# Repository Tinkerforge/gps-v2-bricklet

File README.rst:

GPS Bricklet 2.0
================

This repository contains the firmware source code and the hardware design
files. The documentation generator configs can be found at
https://github.com/Tinkerforge/generators

Repository Content
------------------

software/:
 * examples/: Examples for all supported languages
 * build/: Compiled files
 * src/: Source code of firmware
 * Makefile: Makefile to build project

hardware/:
 * Contains KiCad project files and additionally schematics as PDF

datasheets/:
 * Contains datasheets for sensors and complex ICs that are used

Hardware
--------

The hardware is designed with the open source EDA Suite KiCad
(http://www.kicad.org). Before you are able to open the files,
you have to install the Tinkerforge kicad-libraries
(https://github.com/Tinkerforge/kicad-libraries). You can either clone
them directly in hardware/ or clone them in a separate folder and
symlink them into hardware/
(ln -s kicad_path/kicad-libraries project_path/hardware). After that you
can open the .pro file in hardware/ with KiCad and from there view and
modify the schematics and the PCB layout.

Software
--------

If you want to do your own Brick/Bricklet firmware development we highly
recommend that you use our build environment setup script and read the
tutorial (https://www.tinkerforge.com/en/doc/Tutorials/Tutorial_Build_Environment/Tutorial.html).

To compile the C code we recommend you to install the newest GNU Arm Embedded
Toolchain (https://launchpad.net/gcc-arm-embedded/+download).
You also need to install bricklib2 (https://github.com/Tinkerforge/bricklib2).

You can either clone it directly in software/src/ or clone it in a
separate folder and symlink it into software/src/
(ln -s bricklib_path/bricklib2 project_path/software/src/). Finally make sure to
have CMake installed (http://www.cmake.org/cmake/resources/software.html).

After that you can build the firmware by invoking make in software/.
The firmware (.zbin) can then be found in software/build/ and uploaded
with brickv (click button "Flashing" on start screen).

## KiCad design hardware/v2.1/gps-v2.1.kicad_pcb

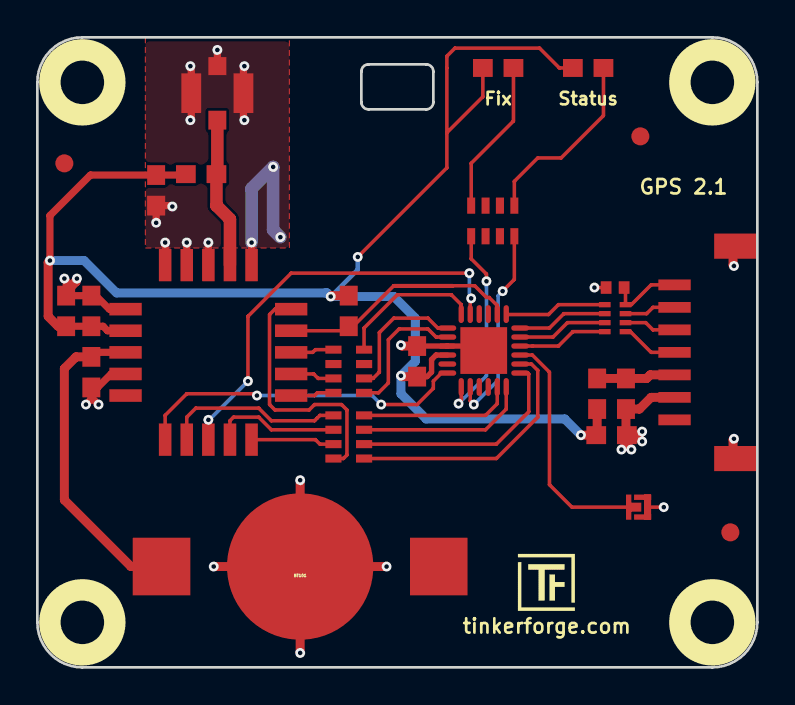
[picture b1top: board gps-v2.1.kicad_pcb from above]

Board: 2 copper layers, 40.0 x 35.0 mm, 32 parts (2 on the bottom side), 35 nets.

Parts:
BT101: Battery; BATTERY_HOLDER_BK870
C1: 220pF; C0402F
C101, C105: 1uF; C0603E
C102: 10uF; C0603E
C103, C104: 100nF; C0603E
C106, C107: 1µF; C0603E
D101: LED blue; D0603E
D102: LED green; D0603E
FB101: FB; C0603E
Fiducial_Mark: VAL**; Fiducial_Mark
Fiducial_Mark#2, Fiducial_Mark#3: VAL**; Fiducial_Mark
L101: 33nH; R0603E
P101: CON-SENSOR; CON-SENSOR2
P103: Boot; SolderJumper
P104: U.FL; U.FL-CON
R102: 1k; R0603E
RP2: 82; 4X0402
RP101, RP102: 270; 0603X4
RP103: 1k; 0603X4
U101: XMC1302-32; QFN24-4x4mm-0.5mm
U102: FireFlyX1
U103, U104, U105, U106: DRILL; DRILL_NP
VAL: WEEE_7mm_back
VAL#2: CE_5mm

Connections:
1PPS: RP101.4, U101.6
GND: BT101.2, C1.2, C101.1, C102.1, C103.1, C104.1, C105.1, C106.1, C107.1, P101.2, P101.EP, P103.1, P104.2, U101.9, U101.EXP, U102.1, U102.3, U102.4, U102.5, U102.6, U102.9
INT: U101.5, U102.13
M-CLK: RP102.6, U101.19
M-CS: RP102.5, U101.20
M-MISO: RP102.8, U101.17
M-MOSI: RP102.7, U101.18
unnamed: C1.1, P101.7, RP2.4
unnamed: C101.2, FB101.2, P101.3
unnamed: D101.2, RP103.1
unnamed: D102.2, RP103.4
unnamed: L101.2, P104.1, U102.2
unnamed: P101.4, RP2.1
unnamed: P101.5, RP2.2
unnamed: P101.6, RP2.3
unnamed: P103.2, U101.21
unnamed: RP101.5, U102.18
unnamed: RP101.7, U102.17
unnamed: RP101.8, U102.16
unnamed: RP102.1, U102.12
unnamed: RP102.2, U102.14
unnamed: RP102.3, U102.15
unnamed: RP102.4, U102.20
unnamed: RP103.5, U101.13
unnamed: RP103.8, U101.14
RESET: R102.2, U101.2, U102.19
RTCM: U101.12, U102.11
RXD: RP101.2, U101.7
S-CLK: RP2.7, U101.23
S-CS: RP2.8, U101.22
S-MISO: RP2.5, U101.1
S-MOSI: RP2.6, U101.24
TXD: RP101.1, U101.8
VBat: BT101.1, C106.2, U102.8
VCC: C102.2, C103.2, C104.2, C105.2, C107.2, D101.1, D102.1, FB101.1, L101.1, R102.1, U101.10, U102.7

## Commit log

2016-09-02 Add readme
2016-09-02 Add initial firmware with bootloader support
2016-09-06 Add system timer
2016-09-06 Better formating for custom command
2016-09-06 Add PRE_BUILD touch and make clean for brickletboot
2016-09-07 Add wait state comment
2016-09-14 datasheets
2016-09-15 Add new source files to Makefile
2016-09-15 Add stub for communication
2016-09-15 Use four DMA channels (2x bootloader SPI and 2x firmware SPI)
2016-09-15 Enable third clock with more precise 8MHz input
2016-09-15 Update logging configuration
2016-09-15 Use new bootloader_ functions to call bootloader init and tick
2016-09-15 Add FireFly X1 driver stub
2016-09-15 Add FireFly X1 driver config
2016-09-15 Add minmea lib (small NMEA parser)
2016-09-22 Add asf_overwrite config
2016-09-22 Change default optimization to Os
2016-09-22 Add asf overwrites
2016-09-22 Use nostartfiles and nono.specs flags for firmware
2016-09-22 Add libgcc static compliles that use division implementation of bootloader
2016-09-22 Update configs
2016-09-22 Add state machine, use bootloader functions
2016-09-22 Remove bootloader_init and debug output (bootloader_init now called during startup)
2016-10-12 Add temporary debug
2016-10-19 adding hardware prototype for new version with co-processor
2016-10-19 change battery holder to version for cr-1025
2016-11-03 Port GPS V2 stub implementation from samd to XMC
2016-11-08 Add automatic build support for bootstrapper
2016-11-09 Fix error in bootstrapper copy logic
2016-11-10 Add firefly and minmea file
2016-11-10 Change default debug pin to boot pin
2016-11-10 Add enhanced bootloader configuration
2016-11-10 Port Firefly X1 configuration from samd to xmc1
2016-11-10 SPI config not needed anymore
2016-11-10 Port Firefly X1 readout implementation from samd to xmc1 (WIP)
2016-11-10 Add firefly init and tick to main again
2016-11-11 remove boot description
2016-11-11 Add stub implementation for API
2016-11-11 Add ringbuffer for incoming data, parse incoming data into structs that hold all of current data
2016-11-11 Use auto-generated communication.c/h
2016-11-14 Change co MCU type to XMC1100_Q024x0016
2016-11-14 Add support for custom cmake config in brickletboot and bootstrapper
2016-11-14 Add custom cmake config
2016-11-14 Use cmake config defines from bricklib2
2016-11-14 Add correct flash origin and size to cmake configs
2016-11-14 Change linker script name
2016-11-17 System timer initialization now done during startup, before main is called
2016-11-17 Use proper indentation
2016-11-17 Remove unused defines
2016-11-17 Fix typo
2016-11-17 Add data pointer, size and limit defines
2016-12-08 Add communication_callback.c to Makefile
2016-12-08 Use 32kb flash size
2016-12-08 Fill in communication data
2016-12-08 Add missing custom bootloader configuration
2016-12-08 Add reset function handling
2016-12-08 Add support for glonass sats
2016-12-08 Add support for detection of new values
2016-12-08 Firmware version should start with 2.0.0
2016-12-08 Remove debugging
2016-12-08 Add constants, restart and new_* variables
2016-12-08 Add communication callback init and tick
2016-12-08 Remove debug
2016-12-08 Simplify callback handling
2016-12-15 fix pin mapping
2016-12-15 Add fix LED configuration and logic
2016-12-15 Add comments for new release version pinouts
2017-01-03 remove silkscreen areas around leds
2017-01-04 drc check, change reset pullup 10k->1k
2017-01-04 add fiducials
2017-01-10 change bricklet connector to 7pole JST GH
2017-01-10 fix grid origin
2017-01-12 change via size, add spi pulldowns for inputs
2017-01-18 ange serial resistor values
2017-01-19 Change MCU to 1302
2017-01-19 Use release version pins
2017-01-19 Add EEPROM emulation size
2017-01-19 Add eeprom page read/write bootloader function define
2017-01-20 Add FireFly X1 datasheet
2017-01-23 Add bootstrapper config
2017-01-31 slot for external antenna added
2017-02-07 add license file
2017-02-07 remove old datasheet
2017-03-07 Fix scale factors for altitude and height to give cm
2017-03-10 Make sure fix LED blinks if fix quality is 0
2017-03-10 Change fix LED to just be on or off to indicate fix
    Also add PPS mode for fix LED.
2017-04-12 Add rx/tx information to allow for hald-fuplex bootstrapper flashing
2017-05-10 Fine-tune naming
2017-05-11 Prepare satellite numbers array for streaming
2017-05-11 Add examples
2017-05-11 Update changelog
2017-05-11 Remove WIP marker
2017-05-31 Report speed correctly as km/h instead of knots
2017-06-02 octave: Use javaObject instead of deprecated java_new
2017-06-16 Add 3d information (tbc)
2017-06-23 Add 3d information (final)
2017-06-23 Add 3d model (*.FCStd and *.STEP)
2017-07-12 add missing schematic
2017-08-31 Reset FireflyX1 if it doesn't talk to us anymore
    If we don't get an interrupt for a long time we first try to
    read from it without interrupt. If we don't get any data back we
    reset the IC.
2017-08-31 Add missing 2.0.1 ref to changelog
2017-09-01 Increase SPI speed to 200kHz
    200kHz is definitely fast enough to receive all data with 10Hz update rate
2017-09-01 Fix ms/us mixup
2017-09-01 Add SBAS enable/disable support and API
2017-09-06 Decrease baudrate to 100000 again
    This seems to be enough for the full 10Hz of data
2017-09-06 Increase version to 2.0.2
2017-09-06 Add changelog for 2.0.2
2017-09-19 specify processor
2017-11-06 update u.fl footprint
2017-11-13 Fix schematic PDF: processor type was unspecified
2017-11-30 Update examples from generator
2017-12-07 mathematica: Also generate .nb files
2018-01-30 Update examples
2018-02-19 javascript: Close div tag correctly
2018-02-20 Cleanup KiCad libraries config
    Ensure LibDir=kicad-libraries and LibName1=tinkerforge.
    Remove special library.
2018-04-18 Initialize logging correctly
2018-04-18 add datasheet
2018-04-18 Add PMTK_A11 datasheet
2018-04-19 Don't use uninitialized data
2018-04-23 Reconfigure SBAS after cold-restart and factory-reset
2018-04-26 Handle different latitude, longitude and altitude resolutions correctly
2018-04-26 Disable debug output
2018-04-26 Add commit ID after the fact
2018-04-26 Fix typo in changelog
2018-05-11 Rename files
2018-05-24 perl: Use strict in examples
2018-05-28 mathematica: Reorder some lines for clearity
2018-06-28 Fix readme
2018-07-11 Add Makefile with docker support
2018-07-11 Remove obsolete generate_makefile scripts
2018-07-11 Update directory structure and build instructions
2018-10-04 Increase version for new release (changes in bricklib2)
2018-10-04 Add rev to changelog
2018-11-06 Add rust examples
2018-11-07 rust: Accept host names for ip connection, fix naming inconsistencies
2018-11-07 rust: Rename callback receivers.
2018-12-14 Add go examples.
2018-12-14 go: Fix printf parameters.
2018-12-18 go: Change import path.
2018-12-18 go: Change import path again.
2018-12-20 rust: Fix result variable names in examples.
2019-01-24 mqtt: Add examples.
2019-01-24 mqtt: Fix example header.
2019-01-24 mqtt: Remove executable bit in example permissions.
2019-01-24 go: Minor example fixes.
2019-01-24 mqtt: Minor example fixes.
2019-03-28 mqtt: Fix whitespace.
2019-04-08 new filter design
2019-04-08 v2.1 ready for prototype
2019-06-13 Fix speed overflow at speeds >=214.74km/h
2019-08-22 c: Adapt to bindings changes
2019-11-14 Use correct scales for VDOP/PDOP calculation.
2019-11-18 change to version 2.1
2019-11-18 remove
2019-11-21 fix weee logo
2019-11-27 add battery description
2019-12-03 Whitespace
2019-12-03 Avoid reset loop by setting last_data_time on reset
    Otherwise the last_data_time check would trigger again immediately
    without leaving the GPS module any time to respond.
2020-01-13 examples: Use python3 input instead of python2 raw_input.
2020-01-13 examples: mqtt: Remove trailing whitespace.
2020-02-28 Add support for hardware version 2.1
    Hardware version 2.0 uses a FireFly X1 module that uses active-low logic
    for its interrupt pin.
    Hardware version 2.1 uses a XM1110 module that uses active-high logic
    for its interrupt pin.
    Assume active-high logic, but fall back to active-low if no interrupt
    occurs for 2 seconds.
2020-02-28 Add commit ref to changelog
2020-04-30 fix 3d data
2020-08-19 Add uc examples.
2020-08-25 uc: Fix whitespace
2020-08-27 uc: Fix warnings.
2020-09-02 uc: Add example driver note.
2020-10-16 uc: Fix divisor type.
2021-10-25 Update KiCad link
    https://www.kicad.org/blog/2021/10/Avoid-links-to-former-kicad-domain/
2022-04-19 examples: uc: Rename TF_HalContext to TF_HAL.
2022-04-27 uc: Adapt to bindings changes
2022-05-10 go: Fix format string
2022-07-06 Add license files.
